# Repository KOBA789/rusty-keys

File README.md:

# RustyKeys

RustyKeys は、組込み Rust 入門に最適な1台を目指して開発された自作キーボードのキットです。

## このリポジトリの内容

このリポジトリは rusty-keys のファームウェアのサンプルコードと、基板の設計データを含んでいます。

- [`firmware`](./firmware): ファームウェアのサンプルコード
- [`pcb`](./pcb): 基板の設計データ

## ビルドガイド

RustyKeys の詳しい仕様や組み立て方についてはビルドガイドをご覧ください。

[RustyKeys ビルドガイド](https://rusty-keys.koba789.com/)

## 入手方法

RustyKeys キットは遊舎工房さんから購入できます。詳しい入手方法は以下のページをご覧ください。

[RustyKeys キットを入手する](https://rusty-keys.koba789.com/get_rusty_keys)

## 質問などは Discussions へ！

組み立てやファームウェア開発に関する質問は GitHub Discussions で受け付けています。
すべての質問にお答えすることを保証するものではありませんが、できる限りサポートしますので困ったときには思い出してみてください。

[RustyKeys Discussions](https://github.com/KOBA789/rusty-keys/discussions)

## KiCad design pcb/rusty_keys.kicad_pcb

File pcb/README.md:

# 基板の設計データ
KiCad 6.0.4 を用いて設計しています。

## 販売されているモデルとの違い
裏面のロゴデータが含まれていないことが唯一の違いです。

※表面の "RustyKeys" ロゴは含まれています。

## パーツリスト(BOM)
調達元は参考情報です。同型・互換の製品であれば他のパーツを使ってもよいでしょう。

- Raspberry Pi Pico x2　(調達元: [遊舎工房](https://shop.yushakobo.jp/products/raspberry-pi-pico), [秋月電子通商](https://akizukidenshi.com/catalog/g/gM-16132/))
- 1N4148 x6 (調達元: [遊舎工房](https://shop.yushakobo.jp/products/a0800di-01-100), [秋月電子通商](https://akizukidenshi.com/catalog/g/gI-16603/))
- L字ピンヘッダ(3P) x1 (調達元: [秋月電子通商](https://akizukidenshi.com/catalog/g/gC-15510/))
- ジャンパ線(ソケット-ソケット 3P) x1 (調達元: [秋月電子通商](https://akizukidenshi.com/catalog/g/gC-15384/))
- ピンヘッダ(40P) x1 (調達元: [秋月電子通商](https://akizukidenshi.com/catalog/g/gC-00167/))
  - 20P x1 でも代用できます (調達元: [秋月電子通商](https://akizukidenshi.com/catalog/g/gC-16590/))
- ゴム足 x4 (調達元: [Amazon.co.jp](https://www.amazon.co.jp/dp/B07QKFW6F6))
  - 直径 5mm x 高さ 2mm 程度のものなら代用できます
  - TRUSCO の TP6R-90 もおすすめです (調達元: [Amazon.co.jp](https://www.amazon.co.jp/dp/B01B4CQVFK))

## 利用しているシンボル・フットプリントライブラリ

- [Keyswitch Kicad Library](https://github.com/perigoso/keyswitch-kicad-library)
- [KiCad-RP-Pico](https://github.com/ncarandini/KiCad-RP-Pico)

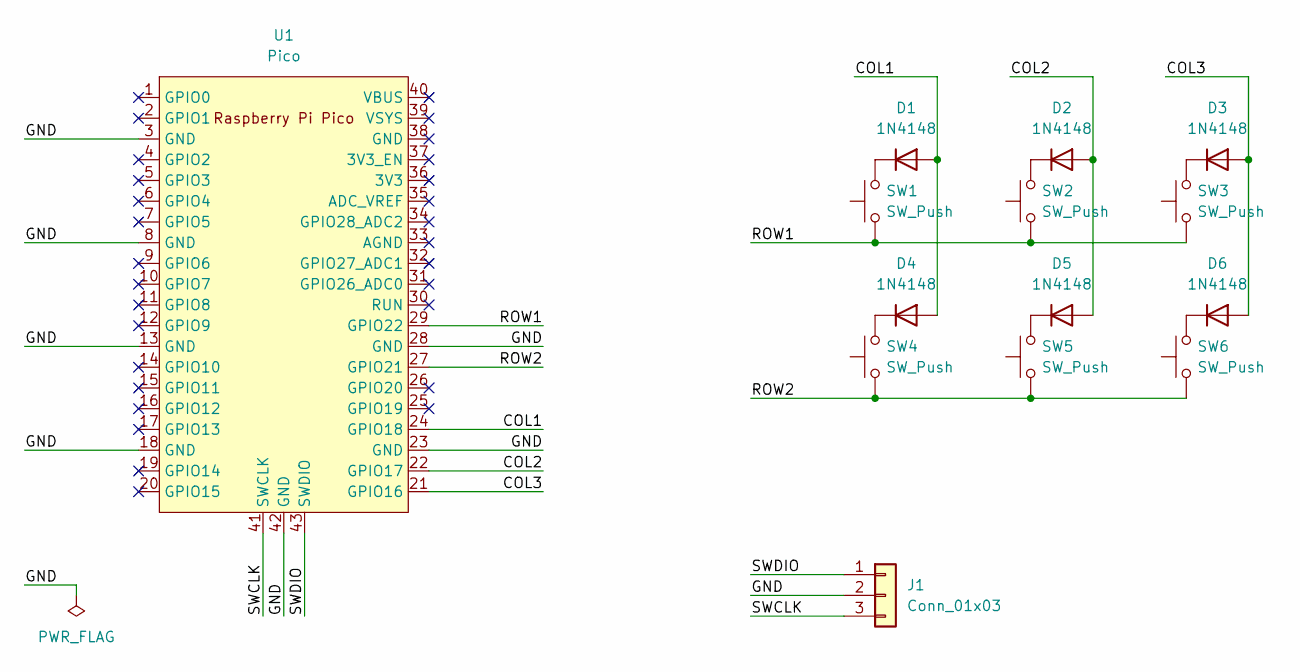
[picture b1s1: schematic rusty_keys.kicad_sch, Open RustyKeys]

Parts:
D1, D2, D3, D4, D5, D6: 1N4148; D_DO-35_SOD27_P7.62mm_Horizontal
J1: Conn_01x03; PinHeader_1x03_P2.54mm_Horizontal
SW1, SW2, SW3, SW4, SW5, SW6: SW_Push; SW_Cherry_MX_PCB_1.00u
U1: Pico; RPi_Pico_SMD_TH

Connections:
/COL1: D1.2 (A), D4.2 (A), U1.24 (GPIO18)
/COL2: D2.2 (A), D5.2 (A), U1.22 (GPIO17)
/COL3: D3.2 (A), D6.2 (A), U1.21 (GPIO16)
/GND: J1.2, U1.3 (GND), U1.8 (GND), U1.13 (GND), U1.18 (GND), U1.23 (GND), U1.28 (GND), U1.42 (GND)
/ROW1: SW1.1, SW2.1, SW3.1, U1.29 (GPIO22)
/ROW2: SW4.1, SW5.1, SW6.1, U1.27 (GPIO21)
/SWCLK: J1.3, U1.41 (SWCLK)
/SWDIO: J1.1, U1.43 (SWDIO)
unnamed: D1.1 (K), SW1.2
unnamed: D2.1 (K), SW2.2
unnamed: D3.1 (K), SW3.2
unnamed: D4.1 (K), SW4.2
unnamed: D5.1 (K), SW5.2
unnamed: D6.1 (K), SW6.2

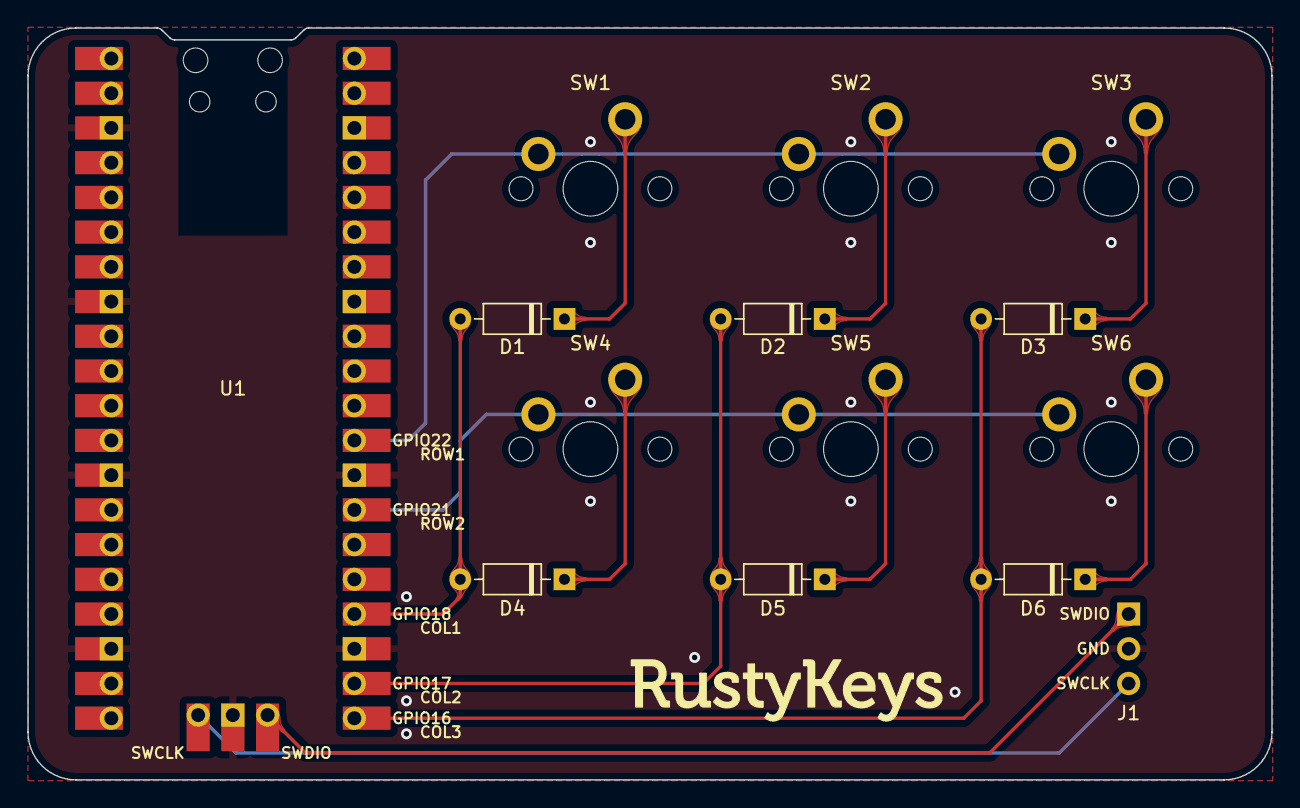
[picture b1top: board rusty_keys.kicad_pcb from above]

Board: 2 copper layers, 91.0 x 55.0 mm, 14 parts (0 on the bottom side), 14 nets.

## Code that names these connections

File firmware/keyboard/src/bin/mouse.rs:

#![no_main]
#![no_std]

use core::convert::Infallible;

use bsp::hal::{self, usb::UsbBus};
use cortex_m::{asm, prelude::*};
use cortex_m_rt::entry;
use defmt_rtt as _;
use embedded_hal::digital::v2::{InputPin, OutputPin};
use embedded_time::duration::Extensions as _;
use hal::pac;
use panic_probe as _;
use rp_pico as bsp;
use usb_device as usbd;
use usbd::{
    class_prelude::UsbBusAllocator,
    device::{UsbDeviceBuilder, UsbVidPid},
};

use usbd_hid::{
    descriptor::{MouseReport, SerializedDescriptor},
    hid_class::{
        HIDClass, HidClassSettings, HidCountryCode, HidProtocol, HidSubClass, ProtocolModeConfig,
    },
};

#[defmt::panic_handler]
fn panic() -> ! {
    cortex_m::asm::udf()
}

pub fn exit() -> ! {
    loop {
        cortex_m::asm::bkpt();
    }
}

#[entry]
fn main() -> ! {
    let mut p = pac::Peripherals::take().unwrap();
    let mut watchdog = hal::Watchdog::new(p.WATCHDOG);
    let clocks = hal::clocks::init_clocks_and_plls(
        bsp::XOSC_CRYSTAL_FREQ,
        p.XOSC,
        p.CLOCKS,
        p.PLL_SYS,
        p.PLL_USB,
        &mut p.RESETS,
        &mut watchdog,
    )
    .ok()
    .unwrap();
    let timer = hal::Timer::new(p.TIMER, &mut p.RESETS);

    let bus = UsbBus::new(
        p.USBCTRL_REGS,
        p.USBCTRL_DPRAM,
        clocks.usb_clock,
        true,
        &mut p.RESETS,
    );
    let bus_allocator = UsbBusAllocator::new(bus);
    let vid_pid = UsbVidPid(0x6666, 0x0789);
    let mut hid = HIDClass::new_with_settings(
        &bus_allocator,
        MouseReport::desc(),
        10,
        HidClassSettings {
            subclass: HidSubClass::NoSubClass,
            protocol: HidProtocol::Mouse,
            config: ProtocolModeConfig::ForceReport,
            locale: HidCountryCode::NotSupported,
        },
    );

    let mut dev = UsbDeviceBuilder::new(&bus_allocator, vid_pid)
        .manufacturer("KOBA789")
        .product("RustyKeys")
        .serial_number("789")
        .build();

    let sio = hal::Sio::new(p.SIO);
    let pins = bsp::Pins::new(p.IO_BANK0, p.PADS_BANK0, sio.gpio_bank0, &mut p.RESETS);

    let col1 = pins.gpio18.into_pull_up_input();
    let col2 = pins.gpio17.into_pull_up_input();
    let col3 = pins.gpio16.into_pull_up_input();
    let mut row1 = pins.gpio22.into_push_pull_output();
    let mut row2 = pins.gpio21.into_push_pull_output();
    let cols: &[Column] = &[&col1, &col2, &col3];
    let rows: &mut [Row] = &mut [&mut row1, &mut row2];

    let mut scan_countdown = timer.count_down();
    scan_countdown.start(10.milliseconds());

    loop {
        dev.poll(&mut [&mut hid]);

        if scan_countdown.wait().is_ok() {
            let state = scan_keys(rows, cols);
            let report = build_report(&state);
            hid.push_input(&report).ok();
        }
        // drop received data
        hid.pull_raw_output(&mut [0; 64]).ok();
    }
}

pub type Column<'a> = &'a dyn InputPin<Error = Infallible>;
pub type Row<'a> = &'a mut dyn OutputPin<Error = Infallible>;
pub type StateMatrix = [[bool; 3]; 2];

fn scan_keys(rows: &mut [Row], cols: &[Column]) -> StateMatrix {
    let mut matrix = [[false; 3]; 2];
    for (row_pin, row_state) in rows.iter_mut().zip(matrix.iter_mut()) {
        row_pin.set_low().unwrap();
        asm::delay(10);
        for (col_pin, col_state) in cols.iter().zip(row_state.iter_mut()) {
            *col_state = col_pin.is_low().unwrap();
        }
        row_pin.set_high().unwrap();
        asm::delay(10);
    }
    matrix
}

fn build_report(matrix: &StateMatrix) -> MouseReport {
    let mut buttons = 0;
    let mut x = 0;
    let mut y = 0;

    if matrix[1][0] {
        x -= 5;
    }
    if matrix[1][2] {
        x += 5;
    }
    if matrix[0][1] {
        y -= 5;
    }
    if matrix[1][1] {
        y += 5;
    }
    if matrix[0][0] {
        buttons += 0b1 << 0; // LEFT CLICK
    }
    if matrix[0][2] {
        buttons += 0b1 << 1; // RIGHT CLICK
    }

    MouseReport {
        buttons,
        x,
        y,
        wheel: 0,
        pan: 0,
    }
}

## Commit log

2022-03-20 hello world
2022-04-24 Restructure directories
2022-04-24 Add some READMEs
2022-04-29 Remove unused import
2022-04-30 Implement simple keyboard
2022-04-30 Remove unused crate
2022-04-30 Add more information about RustyKeys
2022-04-30 Add license
2022-04-30 Add description of firmware/keyboard
2022-05-01 Add KiCad project data
2022-05-01 Fix typo: "游" => "遊"
2022-05-03 Add macro key example
2022-05-03 Add mouse device example
2022-05-03 Fix format
